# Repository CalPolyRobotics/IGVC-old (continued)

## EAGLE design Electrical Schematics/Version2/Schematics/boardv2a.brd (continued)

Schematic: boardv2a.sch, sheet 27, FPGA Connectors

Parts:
TP117, TP143, TP150, TP165, TP166, TP167, TP168, TP169, TP170, TP171, TP172, TP173, TP174, TP175, TP176, TP177, TP178, TP179, TP180, TP181, TP182, TP183, TP184, TP185, TP186, TP187, TP188, TP189, TP190, TP191, TP192, TP193, TP194, TP195, TP196, TP197, TP198, TP199, TP200, TP201, TP202, TP203, TP204, TP205, TP206, TP207, TP208, TP209, TP210, TP211, TP212, TP213, TP214, TP215, TP216, TP217, TP218, TP219, TP220, TP221, TP222, TP223, TP224, TP225, TP228, TP229, TP230, TP231, TP232, TP233: TPPAD1-13; P1-13

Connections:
FPGA_L1N_1: TP207.TP; also elsewhere on the board
FPGA_L1N_2: TP174.TP; also elsewhere on the board
FPGA_L1P_1: TP208.TP; also elsewhere on the board
FPGA_L1P_2: TP176.TP; also elsewhere on the board
FPGA_L2N_2: TP173.TP; also elsewhere on the board
FPGA_L2N_3: TP217.TP; also elsewhere on the board
FPGA_L2P_2: TP175.TP; also elsewhere on the board
FPGA_L2P_3: TP216.TP; also elsewhere on the board
FPGA_L3N_0: TP202.TP; also elsewhere on the board
FPGA_L3N_2: TP117.TP; also elsewhere on the board
FPGA_L3P_0: TP203.TP; also elsewhere on the board
FPGA_L3P_2: TP172.TP; also elsewhere on the board
FPGA_L12N_2: TP185.TP; also elsewhere on the board
FPGA_L12P_2: TP186.TP; also elsewhere on the board
FPGA_L13N_2: TP183.TP; also elsewhere on the board
FPGA_L13P_2: TP184.TP; also elsewhere on the board
FPGA_L30N_2: TP179.TP; also elsewhere on the board
FPGA_L31N_2: TP193.TP; also elsewhere on the board
FPGA_L31P_2: TP194.TP; also elsewhere on the board
FPGA_L32N_1: TP187.TP; also elsewhere on the board
FPGA_L32P_1: TP188.TP; also elsewhere on the board
FPGA_L33N_1: TP218.TP; also elsewhere on the board
FPGA_L33P_1: TP219.TP; also elsewhere on the board
FPGA_L34N_1: TP231.TP; also elsewhere on the board
FPGA_L34P_1: TP233.TP; also elsewhere on the board
FPGA_L37N_3: TP230.TP; also elsewhere on the board
FPGA_L37P_3: TP232.TP; also elsewhere on the board
FPGA_L40N_1: TP177.TP; also elsewhere on the board
FPGA_L40P_1: TP178.TP; also elsewhere on the board
FPGA_L41N_1: TP165.TP; also elsewhere on the board
FPGA_L41N_3: TP228.TP; also elsewhere on the board
FPGA_L41P_1: TP166.TP; also elsewhere on the board
FPGA_L41P_3: TP229.TP; also elsewhere on the board
FPGA_L42N_3: TP224.TP; also elsewhere on the board
FPGA_L42N_GCLK6_TRDY1_1: TP150.TP; also elsewhere on the board
FPGA_L42P_1: TP180.TP; also elsewhere on the board
FPGA_L42P_3: TP225.TP; also elsewhere on the board
FPGA_L43N_1: TP169.TP; also elsewhere on the board
FPGA_L43N_3: TP222.TP; also elsewhere on the board
FPGA_L43P_1: TP170.TP; also elsewhere on the board
FPGA_L43P_3: TP223.TP; also elsewhere on the board
FPGA_L44N_3: TP220.TP; also elsewhere on the board
FPGA_L44P_3: TP221.TP; also elsewhere on the board
FPGA_L45N_1: TP167.TP; also elsewhere on the board
FPGA_L45P_1: TP168.TP; also elsewhere on the board
FPGA_L48N_2: TP191.TP; also elsewhere on the board
FPGA_L48P_2: TP192.TP; also elsewhere on the board
FPGA_L49N_2: TP189.TP; also elsewhere on the board
FPGA_L49N_3: TP171.TP; also elsewhere on the board
FPGA_L49P_2: TP190.TP; also elsewhere on the board
FPGA_L49P_3: TP143.TP; also elsewhere on the board
FPGA_L50N_3: TP181.TP; also elsewhere on the board
FPGA_L50P_3: TP182.TP; also elsewhere on the board
FPGA_L51N_3: TP215.TP; also elsewhere on the board
FPGA_L51P_3: TP214.TP; also elsewhere on the board
FPGA_L52N_3: TP213.TP; also elsewhere on the board
FPGA_L52P_3: TP212.TP; also elsewhere on the board
FPGA_L62N_0: TP201.TP; also elsewhere on the board
FPGA_L62N_2: TP205.TP; also elsewhere on the board
FPGA_L62P_2: TP206.TP; also elsewhere on the board
FPGA_L63N_0: TP199.TP; also elsewhere on the board
FPGA_L63P_0: TP200.TP; also elsewhere on the board
FPGA_L64N_0: TP197.TP; also elsewhere on the board
FPGA_L64N_2: TP211.TP; also elsewhere on the board
FPGA_L64P_0: TP198.TP; also elsewhere on the board
FPGA_L64P_2: TP204.TP; also elsewhere on the board
FPGA_L65N_0: TP195.TP; also elsewhere on the board
FPGA_L65P_0: TP196.TP; also elsewhere on the board
FPGA_L66N_0: TP209.TP; also elsewhere on the board
FPGA_L66P_0: TP210.TP; also elsewhere on the board

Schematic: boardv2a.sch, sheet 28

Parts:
C69: .1uF; 0603-CAP
C118, C119: 10nF; 0603-CAP
D1, D2, D3: GF1; SMA-DO214AC
IC1: MCP41HVX1ST; TSSOP14
IC3: SE555D; SO08
IC5, IC6: 74LVC1G04DBV; SOT23-5
IC7: 4030D; SO14
JP4, JP27: JP1E; JP1
K1: G5V-2
LED2, LED3: GREEN; 1206
LED4: LEDCHIPLED_1206; CHIPLED_1206
Q1, Q2, Q3, Q6, Q19: IRLML2060TRPBFBSS123LT1G; SOT23-3
Q4, Q5, Q18: MOSFET-PCHANNEL; SOT23-3
R11: 150; R0603
R13, R17, R18, R19, R20, R40: 10K; R0603
R14: 1K; MINI_MELF-0102W
R15, R16, R21: 1K; R0603
TP144, TP145, TP146, TP147, TP148, TP149, TP151, TP152, TP153, TP154, TP155, TP156, TP157, TP158, TP159, TP160, TP161, TP162, TP163, TP164: TPB1,27; B1,27
U19, U20: ADUM3442CRWZ; RW_16

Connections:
5V_FNR: D3.K (C), IC1.1 (VL), IC3.4 (R), IC3.8 (V+), IC5.5 (VCC), IC6.5 (VCC), IC7.14 (VDD), K1.1, LED2.A, LED3.A, LED4.A, Q5.3 (D), R16.1, R17.1, TP155.TP, TP158.TP, U19.10 (VE2), U19.16 (VDD2), U20.10 (VE2), U20.16 (VDD2); also elsewhere on the board
CON_FIN: JP4.2; also elsewhere on the board
CON_FNR_HIGH: K1.11 (O); also elsewhere on the board
CON_FNR_POTGND: IC1.10 (V-), IC1.13 (P0A), TP160.TP; also elsewhere on the board
CON_MONB_-: C69.1, C118.2, C119.2, IC1.9 (DGND), IC3.1 (GND), IC5.3 (GND), IC6.3 (GND), IC7.7 (VSS), Q6.2 (S), TP159.TP, U19.9 (GND2_2), U20.9 (GND2_2); also elsewhere on the board
CON_NIN: Q1.2 (S), Q3.2 (S), Q18.1 (G), R17.2, R40.1, TP146.TP; also elsewhere on the board
CON_RIN: JP27.1; also elsewhere on the board
DPOT_ENABLE: R11.2, U19.14 (VOA)
FNR_CON_F: D1.A, JP4.1; also elsewhere on the board
FNR_CON_FD: D1.K (C), Q19.3 (D), R14.2, TP149.TP
FNR_CON_R: D2.A, JP27.2; also elsewhere on the board
FNR_CON_RD: D2.K (C), Q2.3 (D), R15.2, TP148.TP
FNR_CON_THROTTLE+: K1.4, TP162.TP; also elsewhere on the board
FNR_CON_THROTTLE-: K1.13, TP161.TP; also elsewhere on the board
FNR_CON_THROTTLEWIPER: K1.6 (O), TP164.TP; also elsewhere on the board
GND: U19.2 (GND1_2), U19.8 (GND1), U20.2 (GND1_2), U20.8 (GND1); also elsewhere on the board
MCU_+3.3V: U19.1 (VDD1), U19.7 (VE1), U20.1 (VDD1), U20.7 (VE1); also elsewhere on the board
MCU_DPOT_CLK: U20.3 (VIA); also elsewhere on the board
MCU_DPOT_CS: U20.6 (VOD); also elsewhere on the board
MCU_DPOT_CSO: IC1.3 (!CS), U20.11 (VID)
MCU_DPOT_ENABLE: U19.3 (VIA); also elsewhere on the board
MCU_DPOT_MISO: U19.6 (VOD); also elsewhere on the board
MCU_DPOT_MOSI: U19.4 (VIB); also elsewhere on the board
MCU_FNR_DIRECTION: U20.4 (VIB); also elsewhere on the board
MCU_FNR_DIRECTIONO: IC5.2 (I), IC6.2 (I), IC7.2 (I1), R13.1, TP144.TP, U20.13 (VOB)
MCU_FNR_ENABLE: U20.5 (VOC); also elsewhere on the board
MCU_FNR_ENABLEO: R20.1, TP157.TP, U20.12 (VIC)
MCU_MISO: IC1.5 (SDO), U19.11 (VID)
MCU_MOSI: IC1.4 (SDI), U19.13 (VOB)
MCU_SCK: IC1.2 (SCK), U20.14 (VOA)
unnamed: Q5.1 (G), R20.2
unnamed: IC1.12 (P0W), K1.8 (S), TP163.TP
unnamed: LED4.C, R21.1
unnamed: IC1.11 (P0B), IC1.14 (V+), K1.9 (S)
unnamed: Q6.1 (G), R11.1
unnamed: LED2.C, R14.1
unnamed: D3.A, K1.16 (2), Q6.3 (D), R21.2
unnamed: LED3.C, R15.1
unnamed: C119.1, IC3.6 (THR), IC3.7 (DIS), R16.2, TP154.TP
unnamed: C69.2, IC5.4 (O), IC7.1 (I0)
unnamed: IC3.2 (TR), IC7.3 (O), TP156.TP
unnamed: IC3.3 (Q), Q4.1 (G), TP145.TP
unnamed: Q4.3 (D), Q5.2 (S)
unnamed: IC6.4 (O), R18.1, TP153.TP
unnamed: Q4.2 (S), Q18.3 (D)
unnamed: Q1.1 (G), R18.2
unnamed: Q3.1 (G), R13.2, TP152.TP
unnamed: Q18.2 (S), R19.1, R40.2
unnamed: Q1.3 (D), Q2.2 (S)
unnamed: Q3.3 (D), Q19.2 (S), TP151.TP
unnamed: Q2.1 (G), Q19.1 (G), R19.2, TP147.TP
unnamed: C118.1, IC3.5 (CV)

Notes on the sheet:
FNR Block

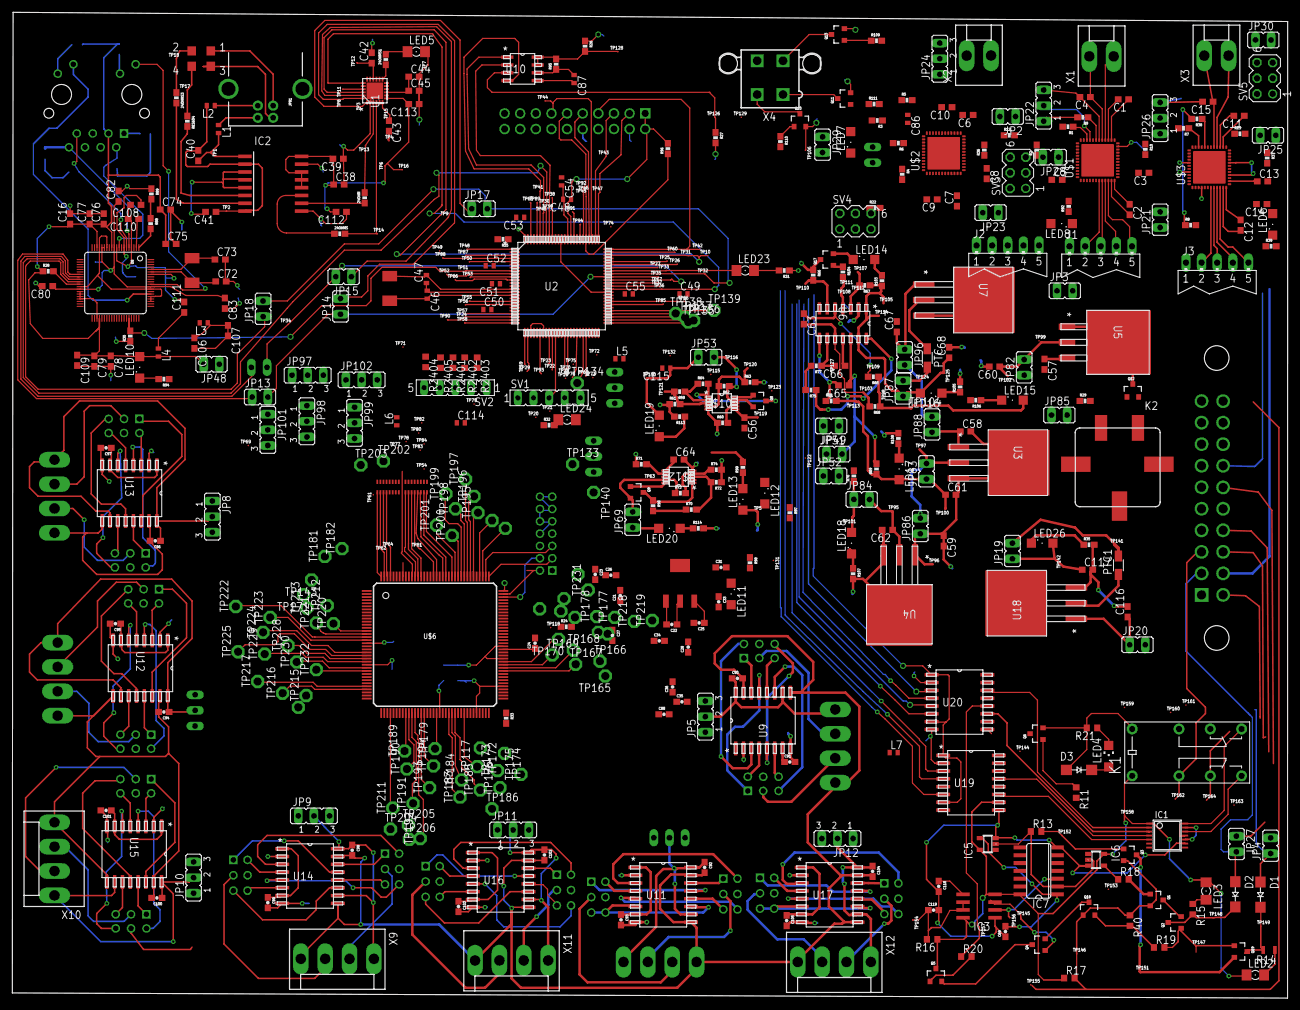
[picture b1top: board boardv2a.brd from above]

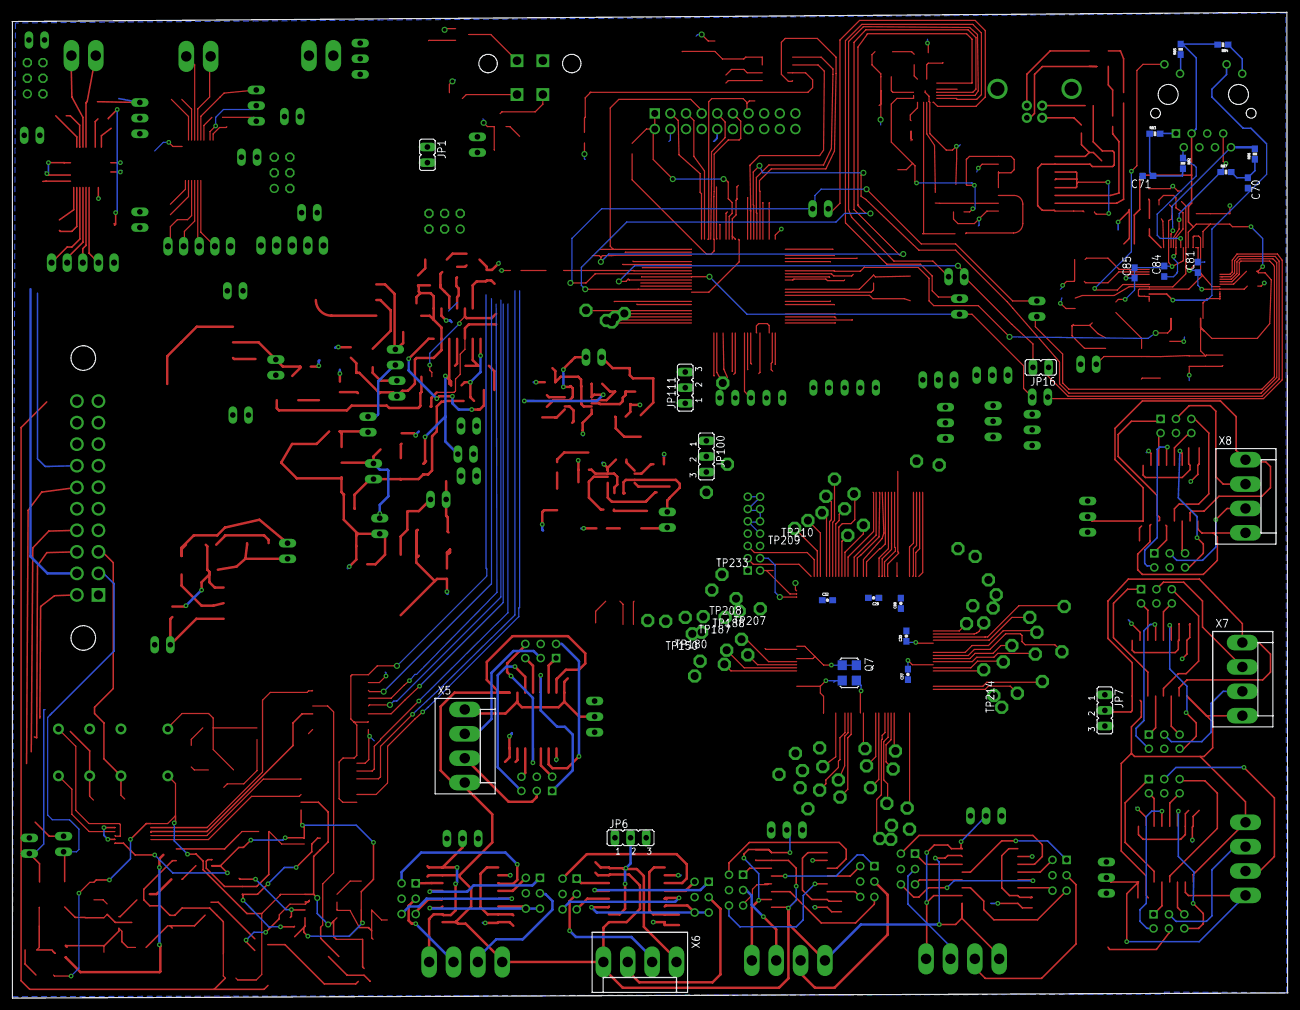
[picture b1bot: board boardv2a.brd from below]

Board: 2 copper layers, 207.3 x 160.2 mm, 623 parts (37 on the bottom side), 513 nets.

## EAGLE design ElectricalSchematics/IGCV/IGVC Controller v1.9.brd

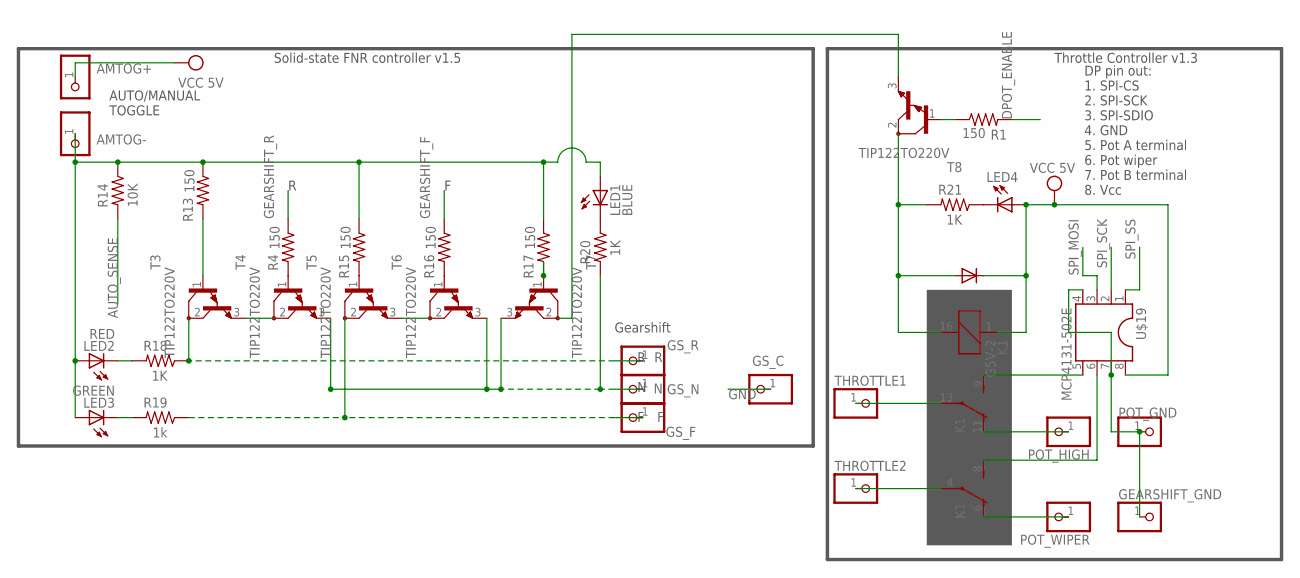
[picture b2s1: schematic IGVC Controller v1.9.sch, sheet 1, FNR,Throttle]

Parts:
AMTOG+: PINHD-1X1; 1X01
AMTOG-: PINHD-1X1; 1X01
D5: 1N4004; DO41-10
GEARSHIFT_GND: PINHD-1X1; 1X01
GS_C: N; 1X01
GS_F: F; 1X01
GS_N: N; 1X01
GS_R: R; 1X01
K1: G5V-2
LED1: BLUE; LED3MM
LED2: RED; LED3MM
LED3: GREEN; LED3MM
LED4: LED3MM
POT_GND: POT_GND; 1X01
POT_HIGH: PINHD-1X1; 1X01
POT_WIPER: PINHD-1X1; 1X01
R1, R4, R13, R15, R16, R17: 150; 0204/5
R14: 10K; 0204/5
R18, R20, R21: 1K; 0204/5
R19: 1k; 0204/5
T3, T4, T5, T6, T7, T8: TIP122TO220V; TO220V
THROTTLE1, THROTTLE2: PINHD-1X1; 1X01
U$19: MCP4131-502E; SO8

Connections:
+5V: AMTOG+.1, D5.C, K1.1, LED4.A, U$19.8 (+5V); also elsewhere on the board
AM_TOGGLE-: AMTOG-.1, LED1.A, LED2.A, LED3.A, R13.1, R14.1, R15.1, R17.1; also elsewhere on the board
AUTO_SENSE: R14.2; also elsewhere on the board
DPOT_ENABLE: R1.2; also elsewhere on the board
FGND: GS_F.1, R19.1, T5.2 (C); also elsewhere on the board
GEARSHIFT_F: R16.1; also elsewhere on the board
GEARSHIFT_R: R4.1; also elsewhere on the board
GND: GEARSHIFT_GND.1, GS_C.1, POT_GND.1, U$19.4 (GND), U$19.7 (A); also elsewhere on the board
N: GS_N.1, R20.2, T4.3 (E), T6.3 (E), T7.3 (E); also elsewhere on the board
unnamed: T7.2 (C), T8.3 (E)
unnamed: R1.1, T8.1 (B)
unnamed: T3.3 (E), T4.2 (C)
unnamed: LED1.K (C), R20.1
unnamed: LED2.K (C), R18.2
unnamed: LED3.K (C), R19.2
unnamed: LED4.K (C), R21.1
unnamed: R13.2, T3.1 (B)
unnamed: R4.2, T4.1 (B)
unnamed: R15.2, T5.1 (B)
unnamed: R16.2, T6.1 (B)
unnamed: T5.3 (E), T6.2 (C)
unnamed: R17.2, T7.1 (B)
unnamed: K1.9 (S), U$19.5 (B)
unnamed: K1.8 (S), U$19.6 (W)
unnamed: D5.A, K1.16 (2), R21.2, T8.2 (C)
POT_HIGH: K1.11 (O), POT_HIGH.1; also elsewhere on the board
POT_WIPER: K1.6 (O), POT_WIPER.1; also elsewhere on the board
RGND: GS_R.1, R18.1, T3.2 (C); also elsewhere on the board
SPI_MOSI: U$19.3 (MOSI); also elsewhere on the board
SPI_SCK: U$19.2 (SCK); also elsewhere on the board
SPI_SS: U$19.1 (SS); also elsewhere on the board
THROTTLE1: K1.13, THROTTLE1.1; also elsewhere on the board
THROTTLE2: K1.4, THROTTLE2.1; also elsewhere on the board

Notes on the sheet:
AUTO/MANUAL TOGGLE
Solid-state FNR controller v1.5
R N F
Gearshift
DP pin out: 1. SPI-CS 2. SPI-SCK 3. SPI-SDIO 4. GND 5. Pot A terminal 6. Pot wiper 7. Pot B terminal 8. Vcc
Throttle Controller v1.3

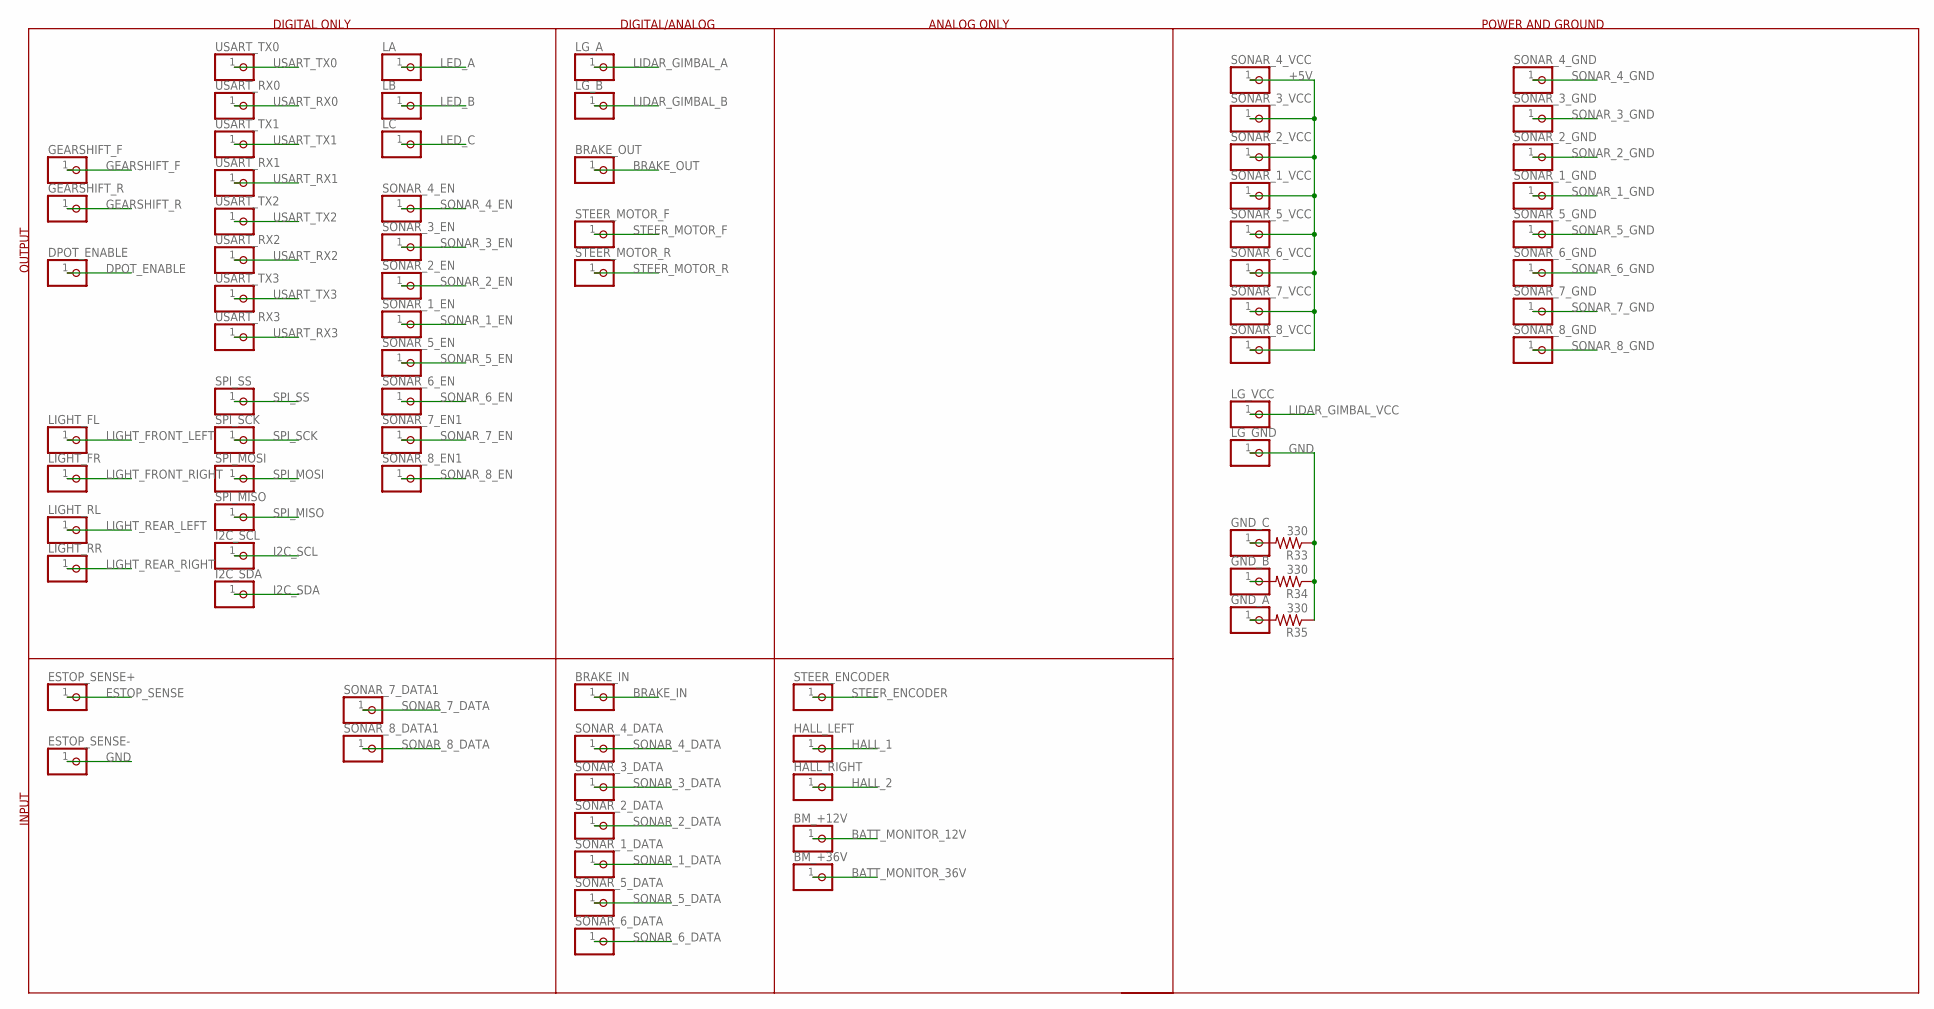
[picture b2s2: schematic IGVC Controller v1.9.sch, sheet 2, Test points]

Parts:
BM_+12V, BM_+36V: PINHD-1X1; 1X01
BRAKE_IN: PINHD-1X1; 1X01
BRAKE_OUT: PINHD-1X1; 1X01
DPOT_ENABLE: PINHD-1X1; 1X01
ESTOP_SENSE+: PINHD-1X1; 1X01
ESTOP_SENSE-: PINHD-1X1; 1X01
GEARSHIFT_F: PINHD-1X1; 1X01
GEARSHIFT_R: PINHD-1X1; 1X01
GND_A: PINHD-1X1; 1X01
GND_B: PINHD-1X1; 1X01
GND_C: PINHD-1X1; 1X01
HALL_LEFT: PINHD-1X1; 1X01
HALL_RIGHT: PINHD-1X1; 1X01
I2C_SCL, I2C_SDA: PINHD-1X1; 1X01
LA: PINHD-1X1; 1X01
LB: PINHD-1X1; 1X01
LC: PINHD-1X1; 1X01
LG_A: PINHD-1X1; 1X01
LG_B: PINHD-1X1; 1X01
LG_GND: PINHD-1X1; 1X01
LG_VCC: PINHD-1X1; 1X01
LIGHT_FL: PINHD-1X1; 1X01
LIGHT_FR: PINHD-1X1; 1X01
LIGHT_RL: PINHD-1X1; 1X01
LIGHT_RR: PINHD-1X1; 1X01
R33, R34, R35: 330; R0603
SONAR_1_DATA, SONAR_1_EN, SONAR_1_GND, SONAR_1_VCC, SONAR_2_DATA, SONAR_2_EN, SONAR_2_GND, SONAR_2_VCC, SONAR_3_DATA, SONAR_3_EN, SONAR_3_GND, SONAR_3_VCC, SONAR_4_DATA, SONAR_4_EN, SONAR_4_GND, SONAR_4_VCC, SONAR_5_DATA, SONAR_5_EN, SONAR_5_GND, SONAR_5_VCC, SONAR_6_DATA, SONAR_6_EN, SONAR_6_GND, SONAR_6_VCC, SONAR_7_DATA1, SONAR_7_EN1, SONAR_7_GND, SONAR_7_VCC, SONAR_8_DATA1, SONAR_8_EN1, SONAR_8_GND, SONAR_8_VCC: PINHD-1X1; 1X01
SPI_MISO: PINHD-1X1; 1X01
SPI_MOSI: PINHD-1X1; 1X01
SPI_SCK: PINHD-1X1; 1X01
SPI_SS: PINHD-1X1; 1X01
STEER_ENCODER: PINHD-1X1; 1X01
STEER_MOTOR_F: PINHD-1X1; 1X01
STEER_MOTOR_R: PINHD-1X1; 1X01
USART_RX0, USART_RX1, USART_RX2, USART_RX3: PINHD-1X1; 1X01
USART_TX0, USART_TX1, USART_TX2, USART_TX3: PINHD-1X1; 1X01

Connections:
+5V: SONAR_1_VCC.1, SONAR_2_VCC.1, SONAR_3_VCC.1, SONAR_4_VCC.1, SONAR_5_VCC.1, SONAR_6_VCC.1, SONAR_7_VCC.1, SONAR_8_VCC.1; also elsewhere on the board
BATT_MONITOR_12V: BM_+12V.1; also elsewhere on the board
BATT_MONITOR_36V: BM_+36V.1; also elsewhere on the board
BRAKE_IN: BRAKE_IN.1; also elsewhere on the board
BRAKE_OUT: BRAKE_OUT.1; also elsewhere on the board
DPOT_ENABLE: DPOT_ENABLE.1; also elsewhere on the board
ESTOP_SENSE: ESTOP_SENSE+.1; also elsewhere on the board
GEARSHIFT_F: GEARSHIFT_F.1; also elsewhere on the board
GEARSHIFT_R: GEARSHIFT_R.1; also elsewhere on the board
GND: ESTOP_SENSE-.1, LG_GND.1, R33.1, R34.1, R35.1; also elsewhere on the board
HALL_1: HALL_LEFT.1; also elsewhere on the board
HALL_2: HALL_RIGHT.1; also elsewhere on the board
I2C_SCL: I2C_SCL.1; also elsewhere on the board
I2C_SDA: I2C_SDA.1; also elsewhere on the board
LED_A: LA.1; also elsewhere on the board
LED_B: LB.1; also elsewhere on the board
LED_C: LC.1; also elsewhere on the board
LIDAR_GIMBAL_A: LG_A.1; also elsewhere on the board
LIDAR_GIMBAL_B: LG_B.1; also elsewhere on the board
LIDAR_GIMBAL_VCC: LG_VCC.1; also elsewhere on the board
LIGHT_FRONT_LEFT: LIGHT_FL.1; also elsewhere on the board
LIGHT_FRONT_RIGHT: LIGHT_FR.1; also elsewhere on the board
LIGHT_REAR_LEFT: LIGHT_RL.1; also elsewhere on the board
LIGHT_REAR_RIGHT: LIGHT_RR.1; also elsewhere on the board
unnamed: GND_C.1, R33.2
unnamed: GND_B.1, R34.2
unnamed: GND_A.1, R35.2
SONAR_1_DATA: SONAR_1_DATA.1; also elsewhere on the board
SONAR_1_EN: SONAR_1_EN.1; also elsewhere on the board
SONAR_1_GND: SONAR_1_GND.1; also elsewhere on the board
SONAR_2_DATA: SONAR_2_DATA.1; also elsewhere on the board
SONAR_2_EN: SONAR_2_EN.1; also elsewhere on the board
SONAR_2_GND: SONAR_2_GND.1; also elsewhere on the board
SONAR_3_DATA: SONAR_3_DATA.1; also elsewhere on the board
SONAR_3_EN: SONAR_3_EN.1; also elsewhere on the board
SONAR_3_GND: SONAR_3_GND.1; also elsewhere on the board
SONAR_4_DATA: SONAR_4_DATA.1; also elsewhere on the board
SONAR_4_EN: SONAR_4_EN.1; also elsewhere on the board
SONAR_4_GND: SONAR_4_GND.1; also elsewhere on the board
SONAR_5_DATA: SONAR_5_DATA.1; also elsewhere on the board
SONAR_5_EN: SONAR_5_EN.1; also elsewhere on the board
SONAR_5_GND: SONAR_5_GND.1; also elsewhere on the board
SONAR_6_DATA: SONAR_6_DATA.1; also elsewhere on the board
SONAR_6_EN: SONAR_6_EN.1; also elsewhere on the board
SONAR_6_GND: SONAR_6_GND.1; also elsewhere on the board
SONAR_7_DATA: SONAR_7_DATA1.1; also elsewhere on the board
SONAR_7_EN: SONAR_7_EN1.1; also elsewhere on the board
SONAR_7_GND: SONAR_7_GND.1; also elsewhere on the board
SONAR_8_DATA: SONAR_8_DATA1.1; also elsewhere on the board
SONAR_8_EN: SONAR_8_EN1.1; also elsewhere on the board
SONAR_8_GND: SONAR_8_GND.1; also elsewhere on the board
SPI_MISO: SPI_MISO.1; also elsewhere on the board
SPI_MOSI: SPI_MOSI.1; also elsewhere on the board
SPI_SCK: SPI_SCK.1; also elsewhere on the board
SPI_SS: SPI_SS.1; also elsewhere on the board
STEER_ENCODER: STEER_ENCODER.1; also elsewhere on the board
STEER_MOTOR_F: STEER_MOTOR_F.1; also elsewhere on the board
STEER_MOTOR_R: STEER_MOTOR_R.1; also elsewhere on the board
USART_RX0: USART_RX0.1; also elsewhere on the board
USART_RX1: USART_RX1.1; also elsewhere on the board
USART_RX2: USART_RX2.1; also elsewhere on the board
USART_RX3: USART_RX3.1; also elsewhere on the board
USART_TX0: USART_TX0.1; also elsewhere on the board
USART_TX1: USART_TX1.1; also elsewhere on the board
USART_TX2: USART_TX2.1; also elsewhere on the board
USART_TX3: USART_TX3.1; also elsewhere on the board

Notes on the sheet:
DIGITAL ONLY
ANALOG ONLY
DIGITAL/ANALOG
INPUT
OUTPUT
POWER AND GROUND
